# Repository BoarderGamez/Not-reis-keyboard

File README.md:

# The Not Reis Keyboard
A split reversable somewhat 40% column staggered keyboard with more keys than normal. The pinky keys are staggered away from the normal layout to be more ergonomic. Aditionally there is an extra row of macro keys to the very end of the keyboard for more productivity. Inspired by Lukas Reis [40ish% keyboard](https://github.com/capitaoananas/40-ish-split-keyboard/) (Also I made it with him lol)

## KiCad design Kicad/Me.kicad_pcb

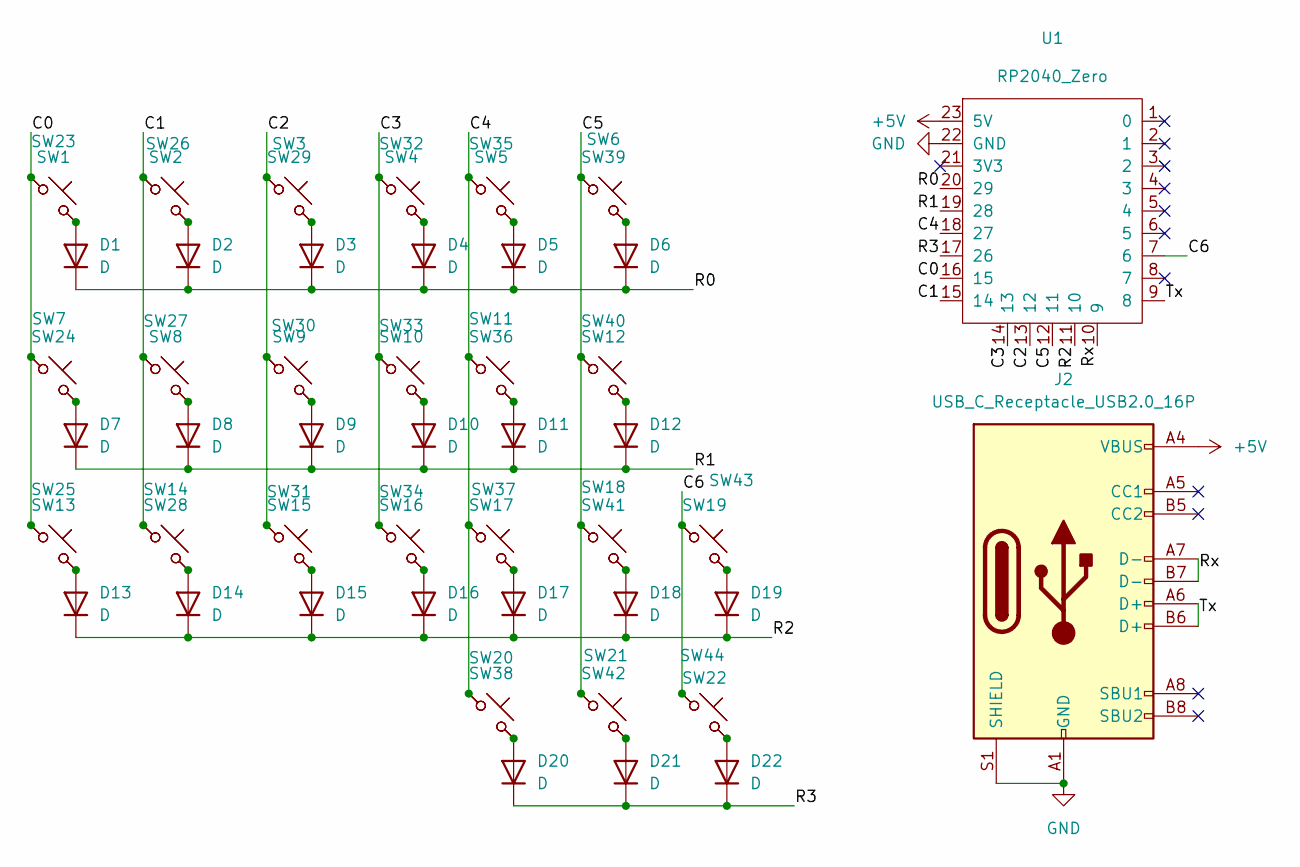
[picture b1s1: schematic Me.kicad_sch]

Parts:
D1, D2, D3, D4, D5, D6, D7, D8, D9, D10, D11, D12, D13, D14, D15, D16, D17, D18, D19, D20, D21, D22: D; Diode_DO-35
J2: USB_C_Receptacle_USB2.0_16P; USB_C_HRO_TYPE-C-31-M-14
SW1, SW2, SW3, SW4, SW5, SW6, SW7, SW8, SW9, SW10, SW11, SW12, SW13, SW14, SW15, SW16, SW17, SW18, SW20, SW23, SW24, SW25, SW26, SW27, SW28, SW29, SW30, SW31, SW32, SW33, SW34, SW35, SW36, SW37, SW38, SW39, SW40, SW41: SW_Push_45deg; MX-Hotswap-1U
SW19, SW21, SW22, SW42, SW43, SW44: SW_Push_45deg; MX-Hotswap-1.5U
U1: RP2040_Zero

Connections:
+5V: J2.A4 (VBUS), J2.A9 (VBUS), J2.B4 (VBUS), J2.B9 (VBUS), U1.23 (5V)
/C0: SW1.1, SW7.1, SW13.1, SW23.1, SW24.1, SW25.1, U1.16 (15)
/C1: SW2.1, SW8.1, SW14.1, SW26.1, SW27.1, SW28.1, U1.15 (14)
/C2: SW3.1, SW9.1, SW15.1, SW29.1, SW30.1, SW31.1, U1.13 (12)
/C3: SW4.1, SW10.1, SW16.1, SW32.1, SW33.1, SW34.1, U1.14 (13)
/C4: SW5.1, SW11.1, SW17.1, SW20.1, SW35.1, SW36.1, SW37.1, SW38.1, U1.18 (27)
/C5: SW6.1, SW12.1, SW18.1, SW21.1, SW39.1, SW40.1, SW41.1, SW42.1, U1.12 (11)
/C6: SW19.1, SW22.1, SW43.1, SW44.1, U1.7 (6)
/R0: D1.1 (K), D2.1 (K), D3.1 (K), D4.1 (K), D5.1 (K), D6.1 (K), U1.20 (29)
/R1: D7.1 (K), D8.1 (K), D9.1 (K), D10.1 (K), D11.1 (K), D12.1 (K), U1.19 (28)
/R2: D13.1 (K), D14.1 (K), D15.1 (K), D16.1 (K), D17.1 (K), D18.1 (K), D19.1 (K), U1.11 (10)
/R3: D20.1 (K), D21.1 (K), D22.1 (K), U1.17 (26)
/Rx: J2.A7 (D-), J2.B7 (D-), U1.10 (9)
/Tx: J2.A6 (D+), J2.B6 (D+), U1.9 (8)
GND: J2.A1 (GND), J2.A12 (GND), J2.B1 (GND), J2.B12 (GND), J2.S1 (SHIELD), U1.22 (GND)
unnamed: D1.2 (A), SW1.2, SW23.2
unnamed: D2.2 (A), SW2.2, SW26.2
unnamed: D3.2 (A), SW3.2, SW29.2
unnamed: D4.2 (A), SW4.2, SW32.2
unnamed: D5.2 (A), SW5.2, SW35.2
unnamed: D6.2 (A), SW6.2, SW39.2
unnamed: D7.2 (A), SW7.2, SW24.2
unnamed: D8.2 (A), SW8.2, SW27.2
unnamed: D9.2 (A), SW9.2, SW30.2
unnamed: D10.2 (A), SW10.2, SW33.2
unnamed: D11.2 (A), SW11.2, SW36.2
unnamed: D12.2 (A), SW12.2, SW40.2
unnamed: D13.2 (A), SW13.2, SW25.2
unnamed: D14.2 (A), SW14.2, SW28.2
unnamed: D15.2 (A), SW15.2, SW31.2
unnamed: D16.2 (A), SW16.2, SW34.2
unnamed: D17.2 (A), SW17.2, SW37.2
unnamed: D18.2 (A), SW18.2, SW41.2
unnamed: D19.2 (A), SW19.2, SW43.2
unnamed: D20.2 (A), SW20.2, SW38.2
unnamed: D21.2 (A), SW21.2, SW42.2
unnamed: D22.2 (A), SW22.2, SW44.2

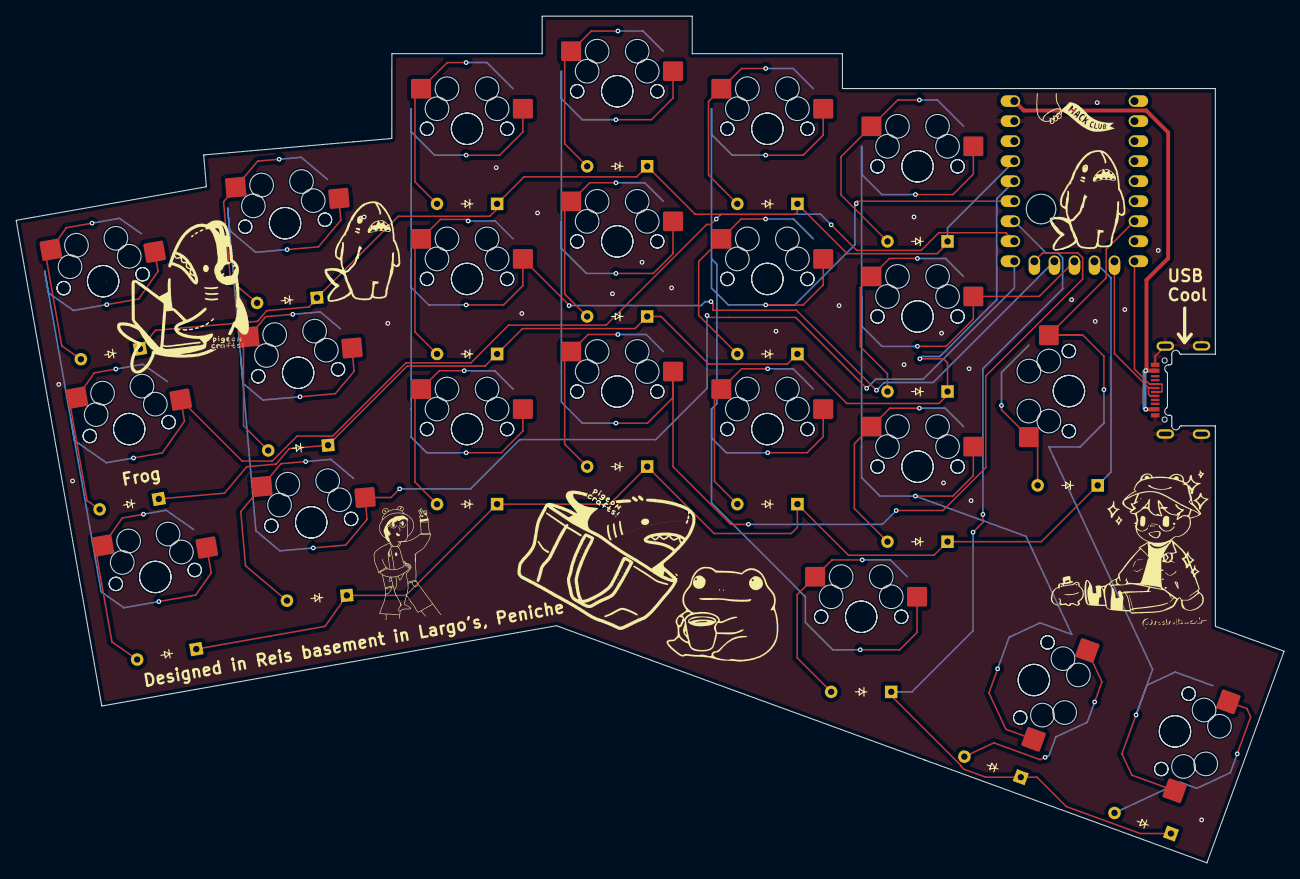
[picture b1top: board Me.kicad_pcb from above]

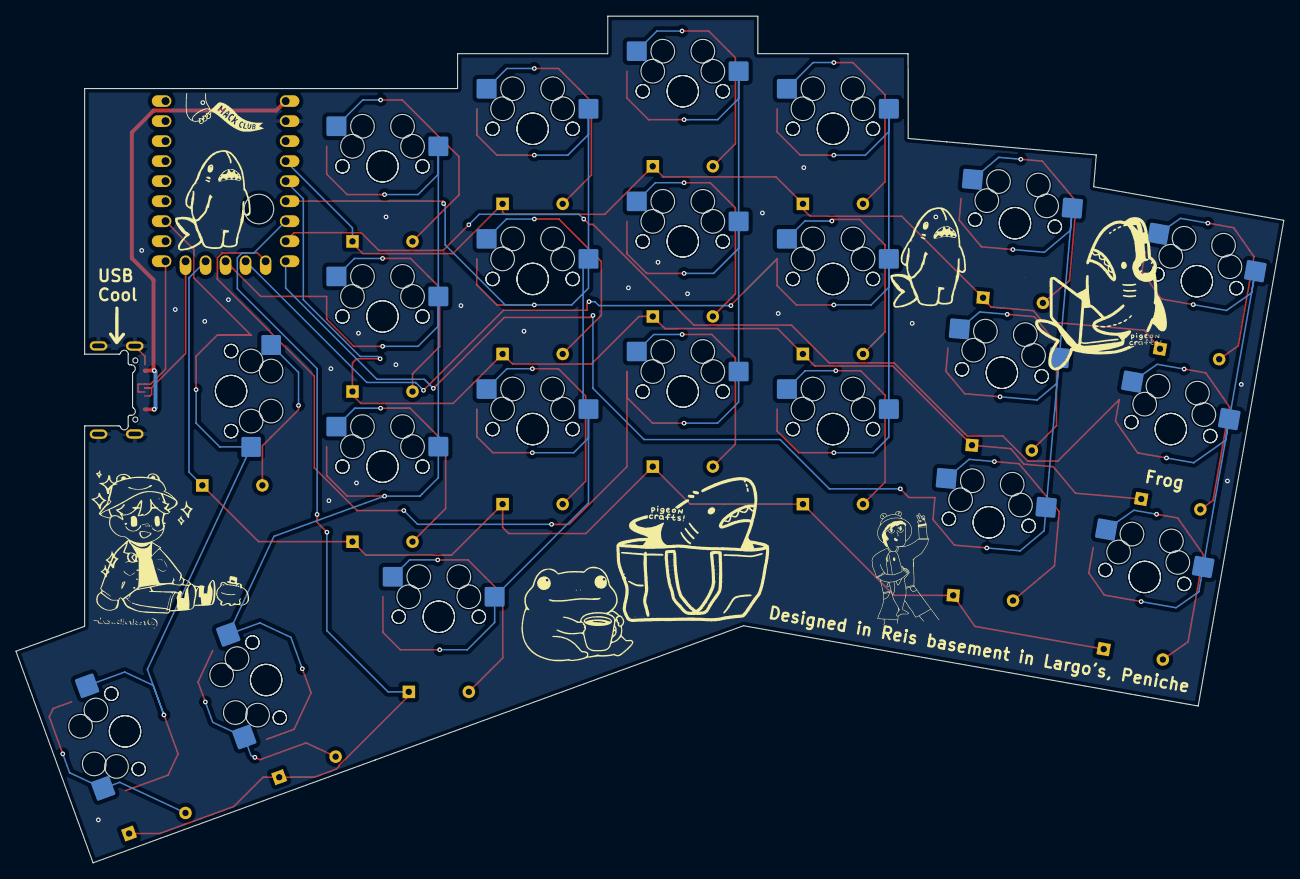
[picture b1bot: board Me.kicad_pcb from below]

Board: 2 copper layers, 160.8 x 107.4 mm, 68 parts (22 on the bottom side), 37 nets.

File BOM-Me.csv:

Comment,Designator,Footprint,LCSC/Part link,Quantity
D,D8,Diode_DO-35,C258182,1
SW_Push_45deg,SW4,MX-Hotswap-1U,http://www.kailh.com/en/Products/Ks/HPC/883.html,1
D,D14,Diode_DO-35,C258182,1
D,D18,Diode_DO-35,C258182,1
D,D16,Diode_DO-35,C258182,1
SW_Push_45deg,SW5,MX-Hotswap-1U,http://www.kailh.com/en/Products/Ks/HPC/883.html,1
SW_Push_45deg,SW2,MX-Hotswap-1U,http://www.kailh.com/en/Products/Ks/HPC/883.html,1
D,D4,Diode_DO-35,C258182,1
SW_Push_45deg,SW21,MX-Hotswap-1.5U,http://www.kailh.com/en/Products/Ks/HPC/883.html,1
D,D1,Diode_DO-35,C258182,1
SW_Push_45deg,SW1,MX-Hotswap-1U,http://www.kailh.com/en/Products/Ks/HPC/883.html,1
SW_Push_45deg,SW6,MX-Hotswap-1U,http://www.kailh.com/en/Products/Ks/HPC/883.html,1
SW_Push_45deg,SW12,MX-Hotswap-1U,http://www.kailh.com/en/Products/Ks/HPC/883.html,1
D,D20,Diode_DO-35,C258182,1
SW_Push_45deg,SW10,MX-Hotswap-1U,http://www.kailh.com/en/Products/Ks/HPC/883.html,1
D,D11,Diode_DO-35,C258182,1
D,D3,Diode_DO-35,C258182,1
D,D21,Diode_DO-35,C258182,1
D,D5,Diode_DO-35,C258182,1
D,D12,Diode_DO-35,C258182,1
SW_Push_45deg,SW16,MX-Hotswap-1U,http://www.kailh.com/en/Products/Ks/HPC/883.html,1
SW_Push_45deg,SW11,MX-Hotswap-1U,http://www.kailh.com/en/Products/Ks/HPC/883.html,1
D,D22,Diode_DO-35,C258182,1
D,D6,Diode_DO-35,C258182,1
D,D13,Diode_DO-35,C258182,1
SW_Push_45deg,SW20,MX-Hotswap-1U,http://www.kailh.com/en/Products/Ks/HPC/883.html,1
SW_Push_45deg,SW17,MX-Hotswap-1U,http://www.kailh.com/en/Products/Ks/HPC/883.html,1
SW_Push_45deg,SW19,MX-Hotswap-1.5U,http://www.kailh.com/en/Products/Ks/HPC/883.html,1
D,D17,Diode_DO-35,C258182,1
SW_Push_45deg,SW15,MX-Hotswap-1U,http://www.kailh.com/en/Products/Ks/HPC/883.html,1
RP2040_Zero,U1,RP2040_Zero,C258182,1
SW_Push_45deg,SW3,MX-Hotswap-1U,http://www.kailh.com/en/Products/Ks/HPC/883.html,1
SW_Push_45deg,SW8,MX-Hotswap-1U,http://www.kailh.com/en/Products/Ks/HPC/883.html,1
SW_Push_45deg,SW7,MX-Hotswap-1U,http://www.kailh.com/en/Products/Ks/HPC/883.html,1
SW_Push_45deg,SW14,MX-Hotswap-1U,http://www.kailh.com/en/Products/Ks/HPC/883.html,1
D,D2,Diode_DO-35,C258182,1
D,D15,Diode_DO-35,C258182,1
SW_Push_45deg,SW22,MX-Hotswap-1.5U,http://www.kailh.com/en/Products/Ks/HPC/883.html,1
D,D9,Diode_DO-35,C258182,1
USB_C_Receptacle_USB2.0_16P,J2,USB_C_HRO_TYPE-C-31-M-14,C223907,1
D,D19,Diode_DO-35,C258182,1
SW_Push_45deg,SW18,MX-Hotswap-1U,http://www.kailh.com/en/Products/Ks/HPC/883.html,1
D,D7,Diode_DO-35,C258182,1
D,D10,Diode_DO-35,C258182,1
SW_Push_45deg,SW9,MX-Hotswap-1U,http://www.kailh.com/en/Products/Ks/HPC/883.html,1
SW_Push_45deg,SW13,MX-Hotswap-1U,http://www.kailh.com/en/Products/Ks/HPC/883.html,1
SW_Push_45deg,SW43,MX-Hotswap-1.5U,http://www.kailh.com/en/Products/Ks/HPC/883.html,1
SW_Push_45deg,SW40,MX-Hotswap-1U,http://www.kailh.com/en/Products/Ks/HPC/883.html,1
SW_Push_45deg,SW32,MX-Hotswap-1U,http://www.kailh.com/en/Products/Ks/HPC/883.html,1
SW_Push_45deg,SW25,MX-Hotswap-1U,http://www.kailh.com/en/Products/Ks/HPC/883.html,1
SW_Push_45deg,SW24,MX-Hotswap-1U,http://www.kailh.com/en/Products/Ks/HPC/883.html,1
SW_Push_45deg,SW39,MX-Hotswap-1U,http://www.kailh.com/en/Products/Ks/HPC/883.html,1
SW_Push_45deg,SW30,MX-Hotswap-1U,http://www.kailh.com/en/Products/Ks/HPC/883.html,1
SW_Push_45deg,SW42,MX-Hotswap-1.5U,http://www.kailh.com/en/Products/Ks/HPC/883.html,1
SW_Push_45deg,SW31,MX-Hotswap-1U,http://www.kailh.com/en/Products/Ks/HPC/883.html,1
SW_Push_45deg,SW37,MX-Hotswap-1U,http://www.kailh.com/en/Products/Ks/HPC/883.html,1
SW_Push_45deg,SW38,MX-Hotswap-1U,http://www.kailh.com/en/Products/Ks/HPC/883.html,1
SW_Push_45deg,SW26,MX-Hotswap-1U,http://www.kailh.com/en/Products/Ks/HPC/883.html,1
SW_Push_45deg,SW28,MX-Hotswap-1U,http://www.kailh.com/en/Products/Ks/HPC/883.html,1
SW_Push_45deg,SW23,MX-Hotswap-1U,http://www.kailh.com/en/Products/Ks/HPC/883.html,1
SW_Push_45deg,SW36,MX-Hotswap-1U,http://www.kailh.com/en/Products/Ks/HPC/883.html,1
SW_Push_45deg,SW34,MX-Hotswap-1U,http://www.kailh.com/en/Products/Ks/HPC/883.html,1
SW_Push_45deg,SW41,MX-Hotswap-1U,http://www.kailh.com/en/Products/Ks/HPC/883.html,1
SW_Push_45deg,SW29,MX-Hotswap-1U,http://www.kailh.com/en/Products/Ks/HPC/883.html,1
SW_Push_45deg,SW35,MX-Hotswap-1U,http://www.kailh.com/en/Products/Ks/HPC/883.html,1
SW_Push_45deg,SW33,MX-Hotswap-1U,http://www.kailh.com/en/Products/Ks/HPC/883.html,1
SW_Push_45deg,SW44,MX-Hotswap-1.5U,http://www.kailh.com/en/Products/Ks/HPC/883.html,1
SW_Push_45deg,SW27,MX-Hotswap-1U,http://www.kailh.com/en/Products/Ks/HPC/883.html,1

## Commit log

2025-10-19 Pcb!
2025-10-19 cover plate 3d print
2025-10-19 Finished bottom
2025-10-20 Added cad files
2025-10-20 new folder
2025-10-20 Added schematics
2025-10-20 added wrl files
2025-10-20 Made readme
2025-10-20 Added bill of materials
2025-10-20 changed name
2025-10-20 Add cost details for keyboard components
    Added detailed cost breakdown for keyboard components including images.
2025-10-21 Revise keycap price and total cost in costs.md
    Updated costs for keycaps and total expenses.
2025-10-22 Revise component costs and total in costs.md
    Updated the costs for components and total expenses.
2025-10-22 Added bom
2025-10-23 Revise README with updated keyboard details
    Updated the keyboard description and image size.
